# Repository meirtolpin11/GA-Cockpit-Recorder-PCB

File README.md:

# GA Cockpit Recorder — TRS+TRRS Adapter

A small adapter PCB and 3D-printed enclosure for recording audio from a
general aviation (GA) cockpit intercom onto a phone, dictaphone, action
camera, or other consumer recorder.

The board breaks out a GA intercom feed into both **3.5 mm TRS** and
**3.5 mm TRRS** jacks so it can be connected to almost any recording device:

- **TRS** — line-style stereo output (standard recorders, line-in inputs).
- **TRRS** — phone-style 4-conductor output (smartphones, headsets that
  expect a mic on the ring/sleeve).

## Important: this is only the adapter

This board does **not** plug directly into the aircraft. To use it you also
need:

1. **A PL splitter** for the cockpit GA jacks (the dual PJ-055 / PJ-068
   "PL" connectors used in GA aircraft). The splitter taps the intercom
   audio without disconnecting the pilot's headset.
2. **A PL-to-TRS cable or adapter** that connects the splitter to this
   adapter board's input jack.

Signal chain:

```
Cockpit GA jacks ── PL splitter ── PL-to-TRS cable ── [this adapter] ── phone / recorder
```

Example of the PL-to-TRS cable that feeds the adapter:

## Connections

| Side | Photo | Description |
|---|---|---|
| Input  |  | TRS jack — connect the PL-to-TRS cable from the PL splitter here. |
| Output |  | TRS + TRRS jacks — connect a phone, action camera, or recorder. |

## Schematic

The full editable KiCad schematic is in
[`pcb/Recorder-TRS+TRRS.kicad_sch`](pcb/Recorder-TRS+TRRS.kicad_sch).

## Repository layout

```
pcb/                          KiCad 9 project
  Recorder-TRS+TRRS.kicad_pro     project file
  Recorder-TRS+TRRS.kicad_sch     schematic
  Recorder-TRS+TRRS.kicad_pcb     PCB layout
  PJ-320A.kicad_sym               vendored symbol (upstream ships only legacy .lib)
  PJ-320A_KiCad_Library/          git submodule -> nathanhborger/PJ-320A_KiCad_Library
  sym-lib-table / fp-lib-table    project-local library tables (KIPRJMOD-relative)

case/                         3D-printable enclosure
  top.stl / middle.stl / bottom.stl
  case.3mf                    source file with all parts

pictures/                     photos of the assembled board and case
```

## Opening the KiCad project

The footprint library is a git submodule, so clone with submodules:

```sh
git clone --recurse-submodules git@github.com:meirtolpin11/GA-Cockpit-Recorder-PCB.git
```

If you already cloned without `--recurse-submodules`:

```sh
git submodule update --init
```

Then open `pcb/Recorder-TRS+TRRS.kicad_pro` in KiCad 9.

The project ships its own `sym-lib-table` and `fp-lib-table` using
`${KIPRJMOD}`-relative paths, so no global KiCad library registration is
needed. If you already have a `PJ-320A` / `PJ-320A_Library` entry in your
global tables you may see a duplicate-nickname warning — the project-local
entry is the one that resolves correctly for this project.

## Ordering the PCB

The board has been successfully manufactured by [JLCPCB](https://jlcpcb.com/)
and that is the recommended way to get one made — it's inexpensive, the
turnaround is fast, and the default 1.6 mm FR-4 stack-up works well for
this design.

Gerbers are not committed to the repo (the KiCad design is the source of
truth). To produce manufacturing files yourself:

1. Open `pcb/Recorder-TRS+TRRS.kicad_pcb` in KiCad.
2. **File → Fabrication Outputs → Gerbers** — use the JLCPCB preset or
   the KiCad defaults.
3. **File → Fabrication Outputs → Drill Files** — Excellon, PTH + NPTH.
4. Zip the resulting folder and upload it to
   [jlcpcb.com](https://jlcpcb.com/) (or another fab of your choice).

## Printing the case

The case prints in three parts (`top.stl`, `middle.stl`, `bottom.stl`).
`case.3mf` is the source file containing all parts together — open it in
your slicer if you'd like to print the set in one job.

## Credits

This design is based on the wiring scheme described in this
[Rivet Bangers forum thread](https://www.rivetbangers.com/forums/viewtopic.php?t=4753).

Special thanks to forum user **bullojm1** for sharing the original idea and
schematic — without that write-up this adapter would not exist. Thank you!

## License

This project is licensed under the **Creative Commons
Attribution-NonCommercial-ShareAlike 4.0 International License**
([CC BY-NC-SA 4.0](https://creativecommons.org/licenses/by-nc-sa/4.0/)).

You are free to share and adapt the design for **non-commercial** purposes,
provided you give credit and release your contributions under the same
license. Commercial use is not permitted without prior written permission.
See [`LICENSE`](LICENSE) for the full text.

The PJ-320A library submodule is © its respective authors and used under
the terms of its own repository.

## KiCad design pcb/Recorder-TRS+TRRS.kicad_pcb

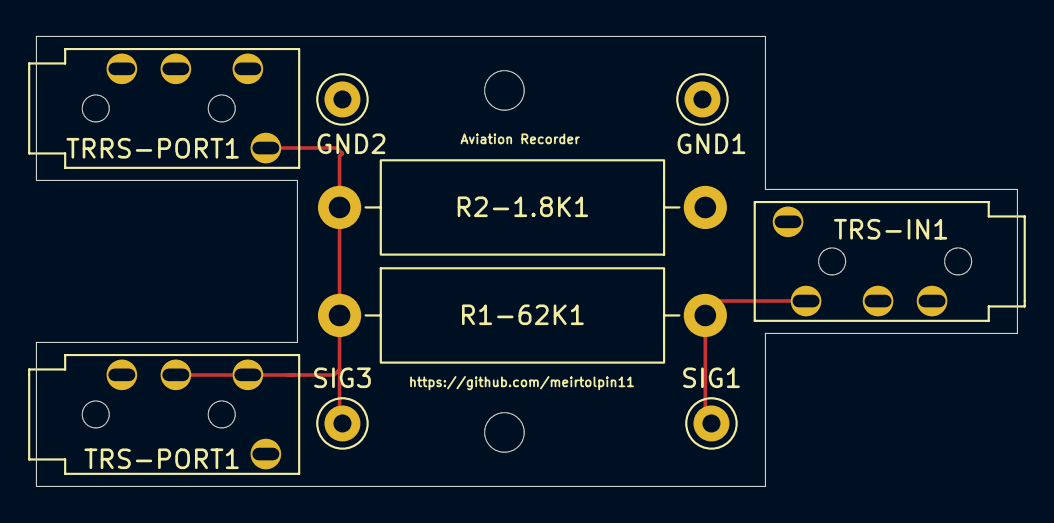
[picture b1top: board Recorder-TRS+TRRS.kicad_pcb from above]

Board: 2 copper layers, 54.5 x 25.0 mm, 9 parts (0 on the bottom side), 3 nets.

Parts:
GND1, GND2: GND; TestPoint_Keystone_5000-5004_Miniature
R1-62K1: 62K; R_Axial_DIN0516_L15.5mm_D5.0mm_P20.32mm_Horizontal
R2-1.8K1: 1.8K; R_Axial_DIN0516_L15.5mm_D5.0mm_P20.32mm_Horizontal
SIG1, SIG3: SIG; TestPoint_Keystone_5000-5004_Miniature
TRRS-PORT1: PJ-320A
TRS-IN1: PJ-320A
TRS-PORT1: PJ-320A

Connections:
/GND: GND1.1, GND2.1, R2-1.8K1.1, TRRS-PORT1.4 (Ring2), TRS-IN1.1 (Sleeve), TRS-PORT1.1 (Sleeve)
/SIGNAL: R1-62K1.2, SIG1.1, TRS-IN1.2 (Tip), TRS-IN1.3 (Ring1)
unnamed: R1-62K1.1, R2-1.8K1.2, SIG3.1, TRRS-PORT1.1 (Sleeve), TRS-PORT1.2 (Tip), TRS-PORT1.3 (Ring1)

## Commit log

2026-05-22 Initial commit: Recorder-TRS+TRRS KiCad project
    PCB design source for the TRS+TRRS Recorder board.
    PJ-320A footprint sourced from upstream as a submodule;
    symbol vendored since upstream only ships legacy .lib format.
2026-05-22 Add case/ folder for enclosure 3D files
    Scope manufacturing-output ignore rules to pcb/ so future case files
    (STEP/STL/etc.) are tracked rather than silently ignored.
2026-05-22 Add enclosure case files (top/middle/bottom STL + 3MF source)
2026-05-22 Add README and project photos
    README documents the adapter purpose, required external parts (PL splitter
    and PL-to-TRS cable), KiCad workflow, and case printing. Credits the
    original wiring scheme from a Rivet Bangers forum thread by user bullojm1.
2026-05-22 Add CC BY-NC-SA 4.0 license and update README license section
2026-05-22 Add schematic image to README
2026-05-22 Recommend JLCPCB for PCB manufacturing
2026-05-25 Updated case setting
